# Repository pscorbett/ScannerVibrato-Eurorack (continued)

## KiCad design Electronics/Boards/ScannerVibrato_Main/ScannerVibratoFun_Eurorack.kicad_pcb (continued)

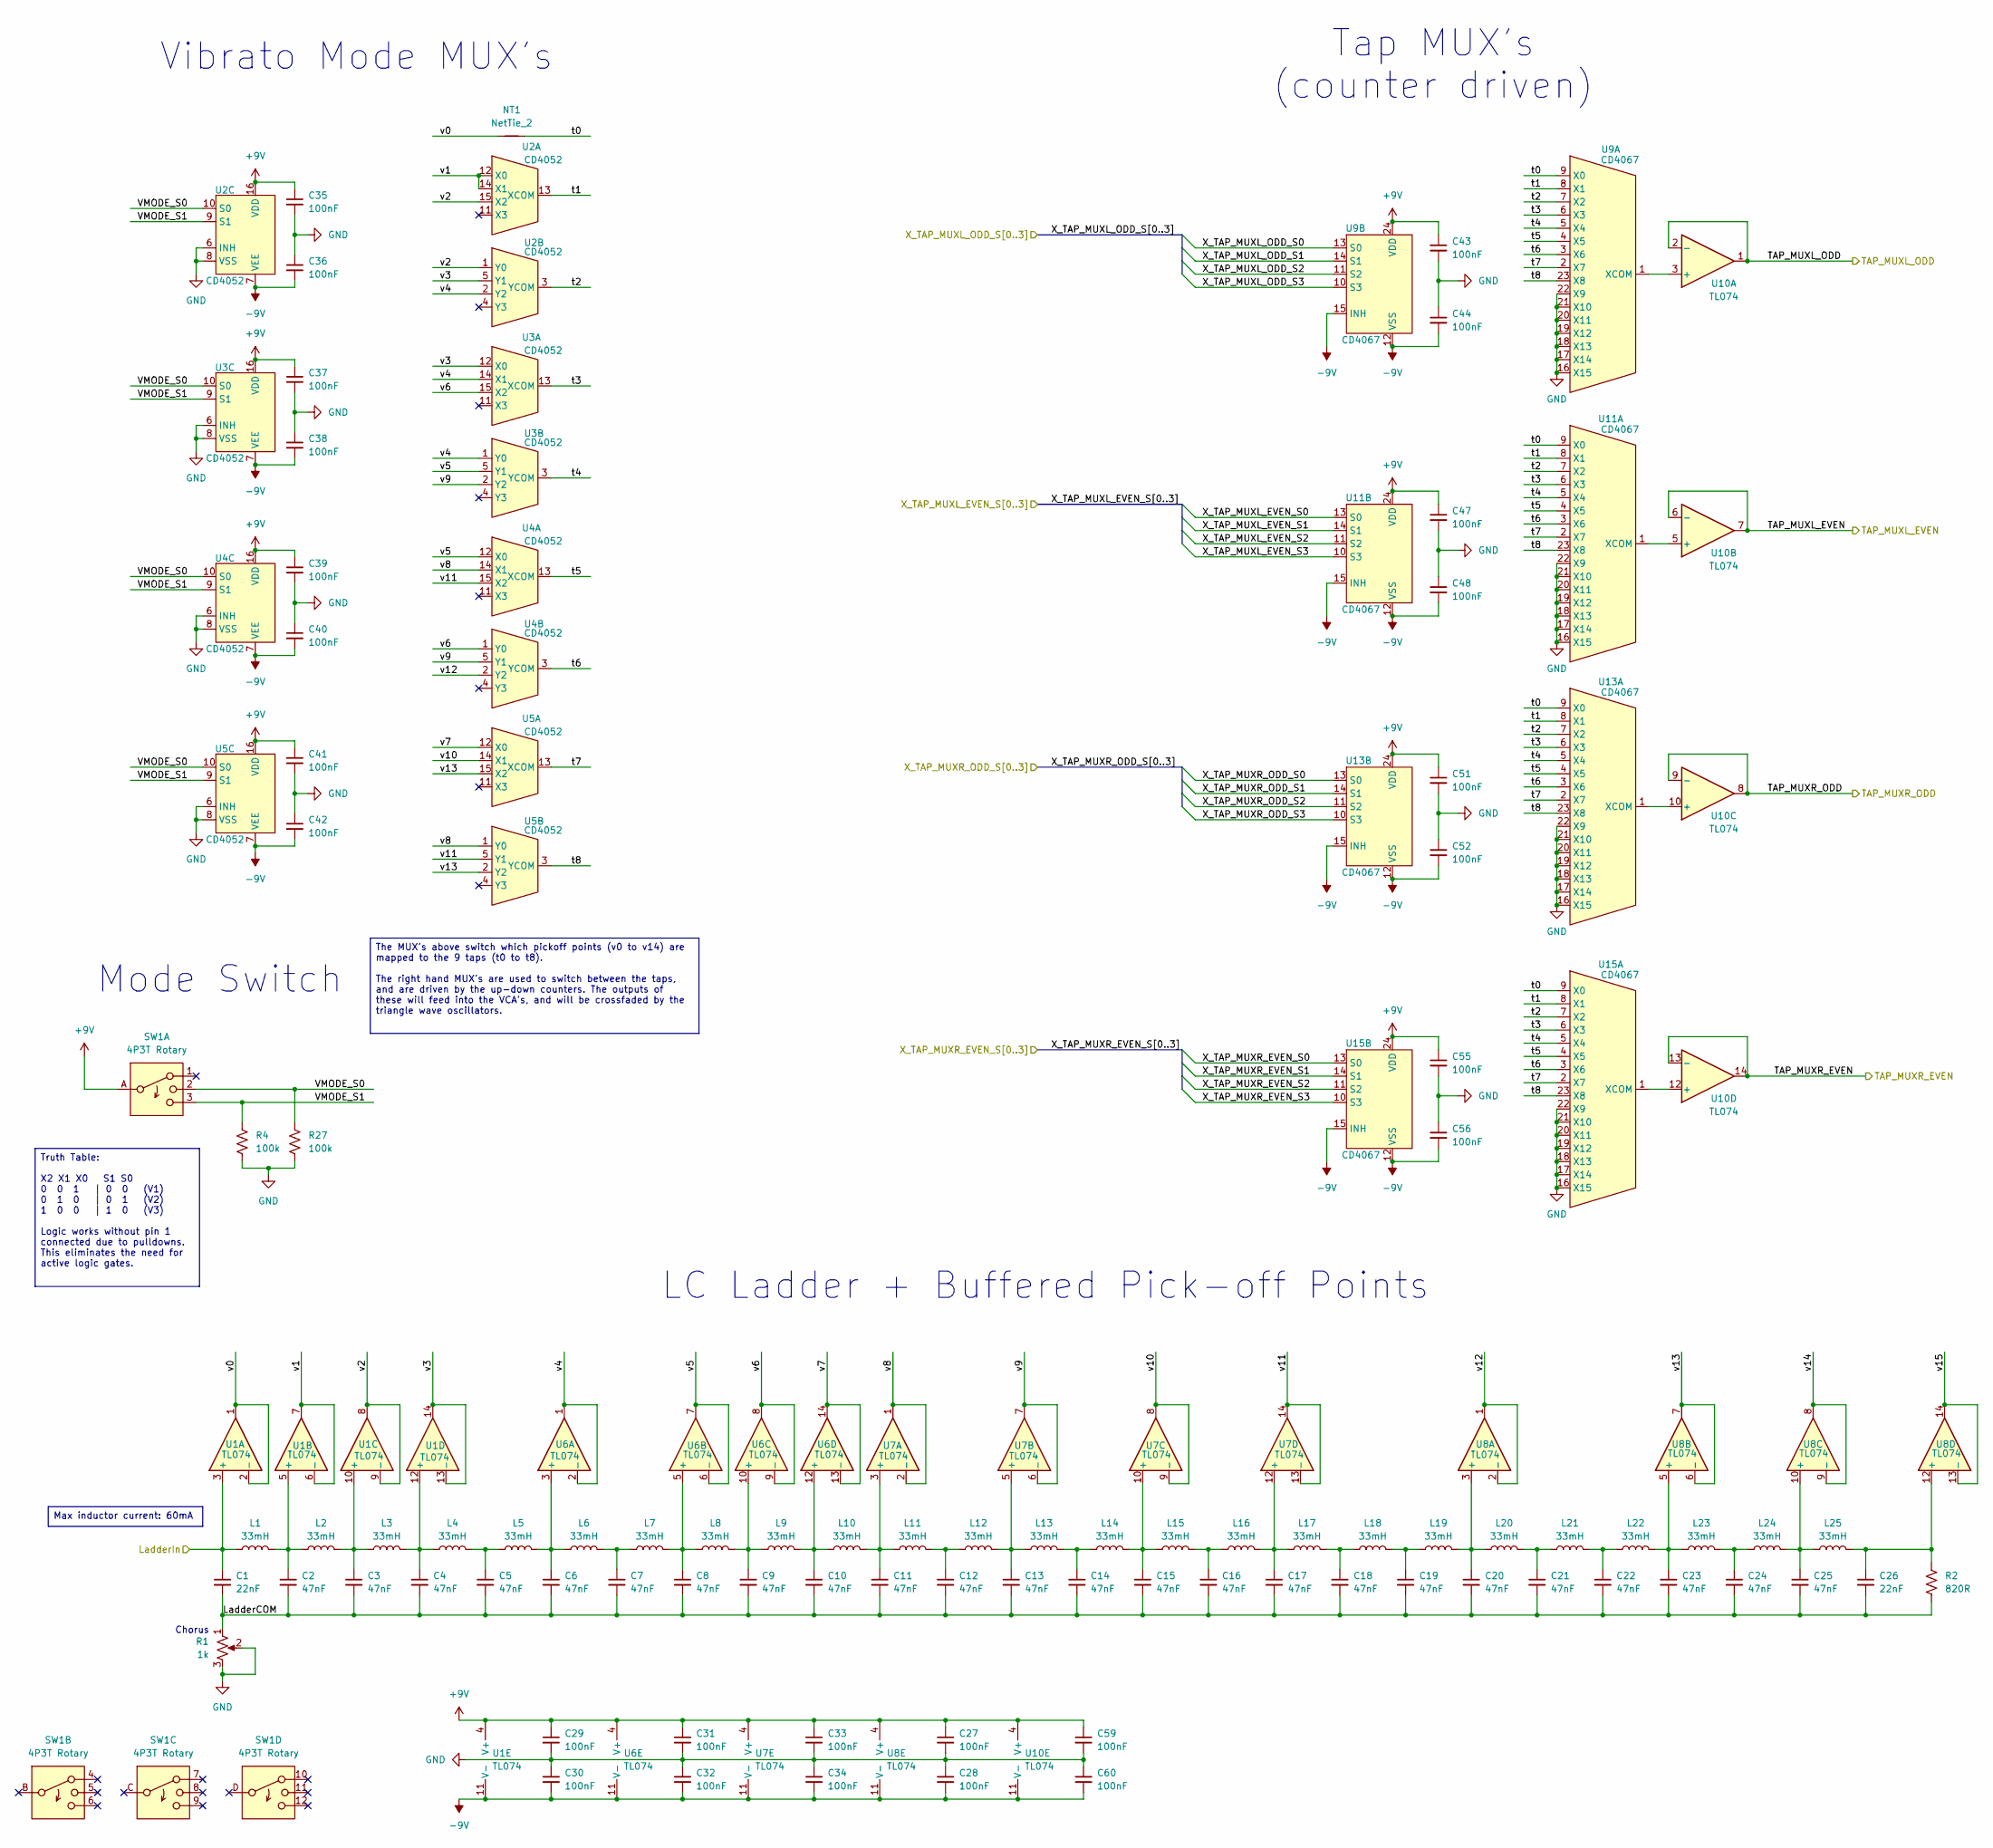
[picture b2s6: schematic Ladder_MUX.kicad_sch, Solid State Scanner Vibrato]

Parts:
C1, C26: 22nF; C_0603_1608Metric
C2, C3, C4, C5, C6, C7, C8, C9, C10, C11, C12, C13, C14, C15, C16, C17, C18, C19, C20, C21, C22, C23, C24, C25: 47nF; C_0603_1608Metric
C27, C28, C29, C30, C31, C32, C33, C34, C35, C36, C37, C38, C39, C40, C41, C42, C43, C44, C47, C48, C51, C52, C55, C56, C59, C60: 100nF; C_0603_1608Metric
L1, L2, L3, L4, L5, L6, L7, L8, L9, L10, L11, L12, L13, L14, L15, L16, L17, L18, L19, L20, L21, L22, L23, L24, L25: 33mH; 1300R_MUR; Part Number 13R336C
NT1: NetTie_2; NetTie-2_SMD_Pad0.5mm
R1: 1k; 16mm-POT-Right-Angle_LL; Part Number RV16AF-4M-15R1-B1K-EV
R2: 820R; R_0603_1608Metric
R4, R27: 100k; R_0603_1608Metric
SW1: 4P3T Rotary; SR2511 1P Hijack; Part Number SR2612F-0403-18R0B-D8-N
U1, U6, U7, U8, U10: TL074; TSSOP-14_4.4x5mm_P0.65mm; Part Number TL074HIPWR
U2, U3, U4, U5: CD4052; TSSOP-16_4.4x5mm_P0.65mm; Part Number CD4052BPWR
U9, U11, U13, U15: CD4067; TSSOP-24_4.4x7.8mm_P0.65mm; Part Number CD4067BPWR

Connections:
+9V: C27.1, C29.1, C31.1, C33.1, C35.1, C37.1, C39.1, C41.1, C43.1, C47.1, C51.1, C55.1, C59.1, SW1.A, U1.4 (V+), U2.16 (VDD), U3.16 (VDD), U4.16 (VDD), U5.16 (VDD), U6.4 (V+), U7.4 (V+), U8.4 (V+), U9.24 (VDD), U10.4 (V+), U11.24 (VDD), U13.24 (VDD), U15.24 (VDD); also elsewhere on the board
-9V: C28.2, C30.2, C32.2, C34.2, C36.2, C38.2, C40.2, C42.2, C44.2, C48.2, C52.2, C56.2, C60.2, U1.11 (V-), U2.7 (VEE), U3.7 (VEE), U4.7 (VEE), U5.7 (VEE), U6.11 (V-), U7.11 (V-), U8.11 (V-), U9.12 (VSS), U9.15 (INH), U10.11 (V-), U11.12 (VSS), U11.15 (INH), U13.12 (VSS), U13.15 (INH), U15.12 (VSS), U15.15 (INH); also elsewhere on the board
/Counters/X_TAP_MUXL_EVEN_S0: U11.13 (S0); also elsewhere on the board
/Counters/X_TAP_MUXL_EVEN_S1: U11.14 (S1); also elsewhere on the board
/Counters/X_TAP_MUXL_EVEN_S2: U11.11 (S2); also elsewhere on the board
/Counters/X_TAP_MUXL_EVEN_S3: U11.10 (S3); also elsewhere on the board
/Counters/X_TAP_MUXL_ODD_S0: U9.13 (S0); also elsewhere on the board
/Counters/X_TAP_MUXL_ODD_S1: U9.14 (S1); also elsewhere on the board
/Counters/X_TAP_MUXL_ODD_S2: U9.11 (S2); also elsewhere on the board
/Counters/X_TAP_MUXL_ODD_S3: U9.10 (S3); also elsewhere on the board
/Counters/X_TAP_MUXR_EVEN_S0: U15.13 (S0); also elsewhere on the board
/Counters/X_TAP_MUXR_EVEN_S1: U15.14 (S1); also elsewhere on the board
/Counters/X_TAP_MUXR_EVEN_S2: U15.11 (S2); also elsewhere on the board
/Counters/X_TAP_MUXR_EVEN_S3: U15.10 (S3); also elsewhere on the board
/Counters/X_TAP_MUXR_ODD_S0: U13.13 (S0); also elsewhere on the board
/Counters/X_TAP_MUXR_ODD_S1: U13.14 (S1); also elsewhere on the board
/Counters/X_TAP_MUXR_ODD_S2: U13.11 (S2); also elsewhere on the board
/Counters/X_TAP_MUXR_ODD_S3: U13.10 (S3); also elsewhere on the board
/Ladder + Mux/LadderCOM: C1.2, C2.2, C3.2, C4.2, C5.2, C6.2, C7.2, C8.2, C9.2, C10.2, C11.2, C12.2, C13.2, C14.2, C15.2, C16.2, C17.2, C18.2, C19.2, C20.2, C21.2, C22.2, C23.2, C24.2, C25.2, C26.2, R1.1, R2.2
/Ladder + Mux/LadderIn: C1.1, L1.1, U1.3 (+); also elsewhere on the board
/Ladder + Mux/TAP_MUXL_EVEN: U10.6 (-), U10.7; also elsewhere on the board
/Ladder + Mux/TAP_MUXL_ODD: U10.1, U10.2 (-); also elsewhere on the board
/Ladder + Mux/TAP_MUXR_EVEN: U10.13 (-), U10.14; also elsewhere on the board
/Ladder + Mux/TAP_MUXR_ODD: U10.8, U10.9 (-); also elsewhere on the board
/Ladder + Mux/VMODE_S0: R27.1, SW1.2, U2.10 (S0), U3.10 (S0), U4.10 (S0), U5.10 (S0)
/Ladder + Mux/VMODE_S1: R4.1, SW1.3, U2.9 (S1), U3.9 (S1), U4.9 (S1), U5.9 (S1)
/Ladder + Mux/t0: NT1.2, U9.9 (X0), U11.9 (X0), U13.9 (X0), U15.9 (X0)
/Ladder + Mux/t1: U2.13 (XCOM), U9.8 (X1), U11.8 (X1), U13.8 (X1), U15.8 (X1)
/Ladder + Mux/t2: U2.3 (YCOM), U9.7 (X2), U11.7 (X2), U13.7 (X2), U15.7 (X2)
/Ladder + Mux/t3: U3.13 (XCOM), U9.6 (X3), U11.6 (X3), U13.6 (X3), U15.6 (X3)
/Ladder + Mux/t4: U3.3 (YCOM), U9.5 (X4), U11.5 (X4), U13.5 (X4), U15.5 (X4)
/Ladder + Mux/t5: U4.13 (XCOM), U9.4 (X5), U11.4 (X5), U13.4 (X5), U15.4 (X5)
/Ladder + Mux/t6: U4.3 (YCOM), U9.3 (X6), U11.3 (X6), U13.3 (X6), U15.3 (X6)
/Ladder + Mux/t7: U5.13 (XCOM), U9.2 (X7), U11.2 (X7), U13.2 (X7), U15.2 (X7)
/Ladder + Mux/t8: U5.3 (YCOM), U9.23 (X8), U11.23 (X8), U13.23 (X8), U15.23 (X8)
/Ladder + Mux/v0: NT1.1, U1.1, U1.2 (-)
/Ladder + Mux/v1: U1.6 (-), U1.7, U2.12 (X0), U2.14 (X1)
/Ladder + Mux/v2: U1.8, U1.9 (-), U2.1 (Y0), U2.15 (X2)
/Ladder + Mux/v3: U1.13 (-), U1.14, U2.5 (Y1), U3.12 (X0)
/Ladder + Mux/v4: U2.2 (Y2), U3.1 (Y0), U3.14 (X1), U6.1, U6.2 (-)
/Ladder + Mux/v5: U3.5 (Y1), U4.12 (X0), U6.6 (-), U6.7
/Ladder + Mux/v6: U3.15 (X2), U4.1 (Y0), U6.8, U6.9 (-)
/Ladder + Mux/v7: U5.12 (X0), U6.13 (-), U6.14
/Ladder + Mux/v8: U4.14 (X1), U5.1 (Y0), U7.1, U7.2 (-)
/Ladder + Mux/v9: U3.2 (Y2), U4.5 (Y1), U7.6 (-), U7.7
/Ladder + Mux/v10: U5.14 (X1), U7.8, U7.9 (-)
/Ladder + Mux/v11: U4.15 (X2), U5.5 (Y1), U7.13 (-), U7.14
/Ladder + Mux/v12: U4.2 (Y2), U8.1, U8.2 (-)
/Ladder + Mux/v13: U5.2 (Y2), U5.15 (X2), U8.6 (-), U8.7
/Ladder + Mux/v14: U8.8, U8.9 (-)
/Ladder + Mux/v15: U8.13 (-), U8.14
GND: C27.2, C28.1, C29.2, C30.1, C31.2, C32.1, C33.2, C34.1, C35.2, C36.1, C37.2, C38.1, C39.2, C40.1, C41.2, C42.1, C43.2, C44.1, C47.2, C48.1, C51.2, C52.1, C55.2, C56.1, C59.2, C60.1, R1.2, R1.3, R4.2, R27.2, U2.6 (INH), U2.8 (VSS), U3.6 (INH), U3.8 (VSS), U4.6 (INH), U4.8 (VSS), U5.6 (INH), U5.8 (VSS), U9.16 (X15), U9.17 (X14), U9.18 (X13), U9.19 (X12), U9.20 (X11), U9.21 (X10), U9.22 (X9), U11.16 (X15), U11.17 (X14), U11.18 (X13), U11.19 (X12), U11.20 (X11), U11.21 (X10), U11.22 (X9), U13.16 (X15), U13.17 (X14), U13.18 (X13), U13.19 (X12), U13.20 (X11), U13.21 (X10), U13.22 (X9), U15.16 (X15), U15.17 (X14), U15.18 (X13), U15.19 (X12), U15.20 (X11), U15.21 (X10), U15.22 (X9); also elsewhere on the board
unnamed: C5.1, L4.2, L5.1
unnamed: C7.1, L6.2, L7.1
unnamed: C12.1, L11.2, L12.1
unnamed: C14.1, L13.2, L14.1
unnamed: C16.1, L15.2, L16.1
unnamed: C18.1, L17.2, L18.1
unnamed: C19.1, L18.2, L19.1
unnamed: C21.1, L20.2, L21.1
unnamed: C22.1, L21.2, L22.1
unnamed: C24.1, L23.2, L24.1
unnamed: C2.1, L1.2, L2.1, U1.5 (+)
unnamed: C3.1, L2.2, L3.1, U1.10 (+)
unnamed: C4.1, L3.2, L4.1, U1.12 (+)
unnamed: C6.1, L5.2, L6.1, U6.3 (+)
unnamed: C8.1, L7.2, L8.1, U6.5 (+)
unnamed: C9.1, L8.2, L9.1, U6.10 (+)
unnamed: C10.1, L9.2, L10.1, U6.12 (+)
unnamed: C11.1, L10.2, L11.1, U7.3 (+)
unnamed: C13.1, L12.2, L13.1, U7.5 (+)
unnamed: C15.1, L14.2, L15.1, U7.10 (+)
unnamed: C17.1, L16.2, L17.1, U7.12 (+)
unnamed: C20.1, L19.2, L20.1, U8.3 (+)
unnamed: C23.1, L22.2, L23.1, U8.5 (+)
unnamed: C25.1, L24.2, L25.1, U8.10 (+)
unnamed: C26.1, L25.2, R2.1, U8.12 (+)
unnamed: U9.1 (XCOM), U10.3 (+)
unnamed: U10.5 (+), U11.1 (XCOM)
unnamed: U10.10 (+), U13.1 (XCOM)
unnamed: U10.12 (+), U15.1 (XCOM)

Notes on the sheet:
Tap MUX's (counter driven)
Mode Switch
Vibrato Mode MUX's
Chorus
LC Ladder + Buffered Pick-off Points
Truth Table: X2 X1 X0 S1 S0 0 0 1 | 0 0 (V1) 0 1 0 | 0 1 (V2) 1 0 0 | 1 0 (V3) Logic works without pin 1 connected due to pulldowns. This eliminates the need for active logic gates.
The MUX's above switch which pickoff points (v0 to v14) are mapped to the 9 taps (t0 to t8). The right hand MUX's are used to switch between the taps, and are driven by the up-down counters. The outputs of these will feed into the VCA's, and will be crossfaded by the triangle wave oscillators.
Max inductor current: 60mA

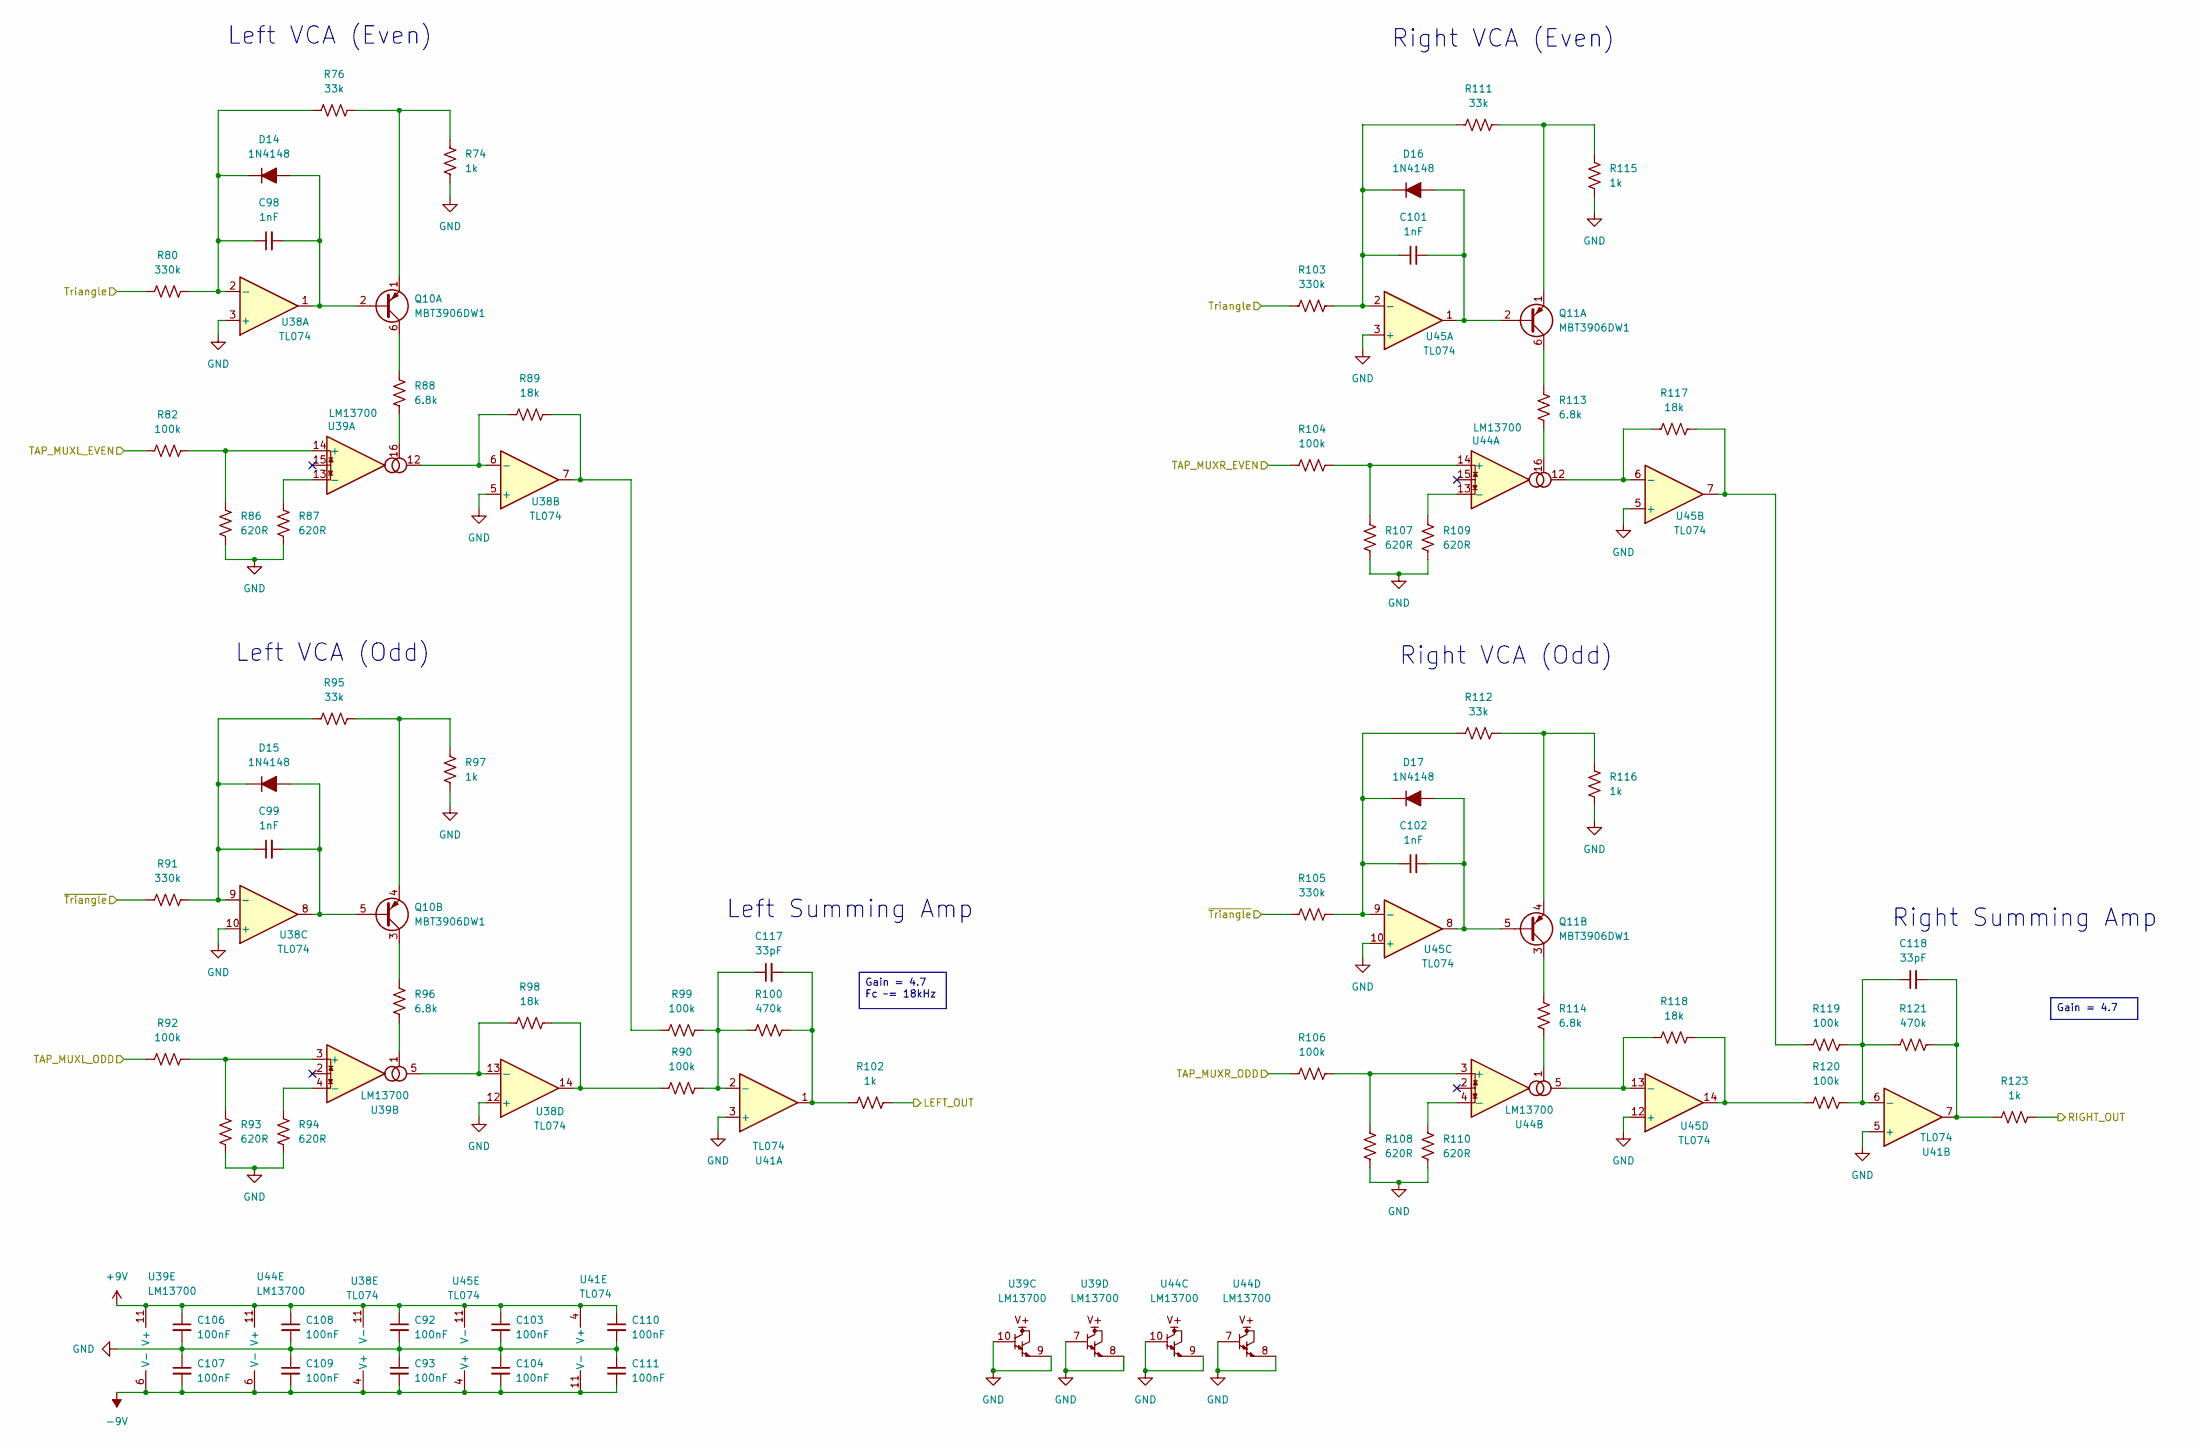
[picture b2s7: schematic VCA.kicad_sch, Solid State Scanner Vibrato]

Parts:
C92, C93, C103, C104, C106, C107, C108, C109, C110, C111: 100nF; C_0603_1608Metric
C98, C99, C101, C102: 1nF; C_0603_1608Metric
C117, C118: 33pF; C_0603_1608Metric
D14, D15, D16, D17: 1N4148; D_SOD-523; Part Number 1N4148WT
Q10, Q11: MBT3906DW1; SOT-363_SC-70-6; Part Number MBT3906DW1T1G
R74, R97, R102, R115, R116, R123: 1k; R_0603_1608Metric
R76, R95, R111, R112: 33k; R_0603_1608Metric
R80, R91, R103, R105: 330k; R_0603_1608Metric
R82, R90, R92, R99, R104, R106, R119, R120: 100k; R_0603_1608Metric
R86, R87, R93, R94, R107, R108, R109, R110: 620R; R_0603_1608Metric
R88, R96, R113, R114: 6.8k; R_0603_1608Metric
R89, R98, R117, R118: 18k; R_0603_1608Metric
R100, R121: 470k; R_0603_1608Metric
U38, U41, U45: TL074; TSSOP-14_4.4x5mm_P0.65mm; Part Number TL074HIPWR
U39, U44: LM13700; SOIC-16_3.9x9.9mm_P1.27mm; Part Number LM13700MX/NOPB

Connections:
+9V: C92.1, C103.1, C106.1, C108.1, C110.1, U38.11 (V-), U39.11 (V+), U41.4 (V+), U44.11 (V+), U45.11 (V-); also elsewhere on the board
-9V: C93.2, C104.2, C107.2, C109.2, C111.2, U38.4 (V+), U39.6 (V-), U41.11 (V-), U44.6 (V-), U45.4 (V+); also elsewhere on the board
/LED Array/Triangle: R80.2, R103.2; also elsewhere on the board
/LED Array/~Triangle: R91.2, R105.2; also elsewhere on the board
/Ladder + Mux/TAP_MUXL_EVEN: R82.2; also elsewhere on the board
/Ladder + Mux/TAP_MUXL_ODD: R92.2; also elsewhere on the board
/Ladder + Mux/TAP_MUXR_EVEN: R104.2; also elsewhere on the board
/Ladder + Mux/TAP_MUXR_ODD: R106.2; also elsewhere on the board
/VCAs/LEFT_OUT: R102.1; also elsewhere on the board
/VCAs/RIGHT_OUT: R123.1; also elsewhere on the board
GND: C92.2, C93.1, C103.2, C104.1, C106.2, C107.1, C108.2, C109.1, C110.2, C111.1, R74.1, R86.1, R87.1, R93.1, R94.1, R97.1, R107.1, R108.1, R109.1, R110.1, R115.1, R116.1, U38.3 (+), U38.5 (+), U38.10 (+), U38.12 (+), U39.7, U39.8, U39.9, U39.10, U41.3 (+), U41.5 (+), U44.7, U44.8, U44.9, U44.10, U45.3 (+), U45.5 (+), U45.10 (+), U45.12 (+); also elsewhere on the board
unnamed: C117.2, R100.1, R102.2, U41.1
unnamed: C118.2, R121.1, R123.2, U41.7
unnamed: C98.2, D14.2 (A), Q10.2 (B1), U38.1
unnamed: C98.1, D14.1 (K), R76.2, R80.1, U38.2 (-)
unnamed: C99.2, D15.2 (A), Q10.5 (B2), U38.8
unnamed: C99.1, D15.1 (K), R91.1, R95.2, U38.9 (-)
unnamed: C101.2, D16.2 (A), Q11.2 (B1), U45.1
unnamed: C101.1, D16.1 (K), R103.1, R111.2, U45.2 (-)
unnamed: C102.2, D17.2 (A), Q11.5 (B2), U45.8
unnamed: C102.1, D17.1 (K), R105.1, R112.2, U45.9 (-)
unnamed: Q10.6 (C1), R88.2
unnamed: Q10.1 (E1), R74.2, R76.1
unnamed: Q10.3 (C2), R96.2
unnamed: Q10.4 (E2), R95.1, R97.2
unnamed: Q11.6 (C1), R113.2
unnamed: Q11.1 (E1), R111.1, R115.2
unnamed: Q11.3 (C2), R114.2
unnamed: Q11.4 (E2), R112.1, R116.2
unnamed: R88.1, U39.16
unnamed: R89.1, R99.2, U38.7
unnamed: R90.2, R98.1, U38.14
unnamed: R96.1, U39.1
unnamed: R113.1, U44.16
unnamed: R114.1, U44.1
unnamed: R117.1, R119.2, U45.7
unnamed: R118.1, R120.2, U45.14
unnamed: R89.2, U38.6 (-), U39.12
unnamed: R98.2, U38.13 (-), U39.5
unnamed: R82.1, R86.2, U39.14 (+)
unnamed: R87.2, U39.13 (-)
unnamed: R92.1, R93.2, U39.3 (+)
unnamed: R94.2, U39.4 (-)
unnamed: C117.1, R90.1, R99.1, R100.2, U41.2 (-)
unnamed: C118.1, R119.1, R120.1, R121.2, U41.6 (-)
unnamed: R104.1, R107.2, U44.14 (+)
unnamed: R109.2, U44.13 (-)
unnamed: R106.1, R108.2, U44.3 (+)
unnamed: R110.2, U44.4 (-)
unnamed: R117.2, U44.12, U45.6 (-)
unnamed: R118.2, U44.5, U45.13 (-)

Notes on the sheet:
Right VCA (Even)
Left VCA (Odd)
Right Summing Amp
Right VCA (Odd)
Left Summing Amp
Left VCA (Even)
Gain = 4.7 Fc ~= 18kHz
Gain = 4.7

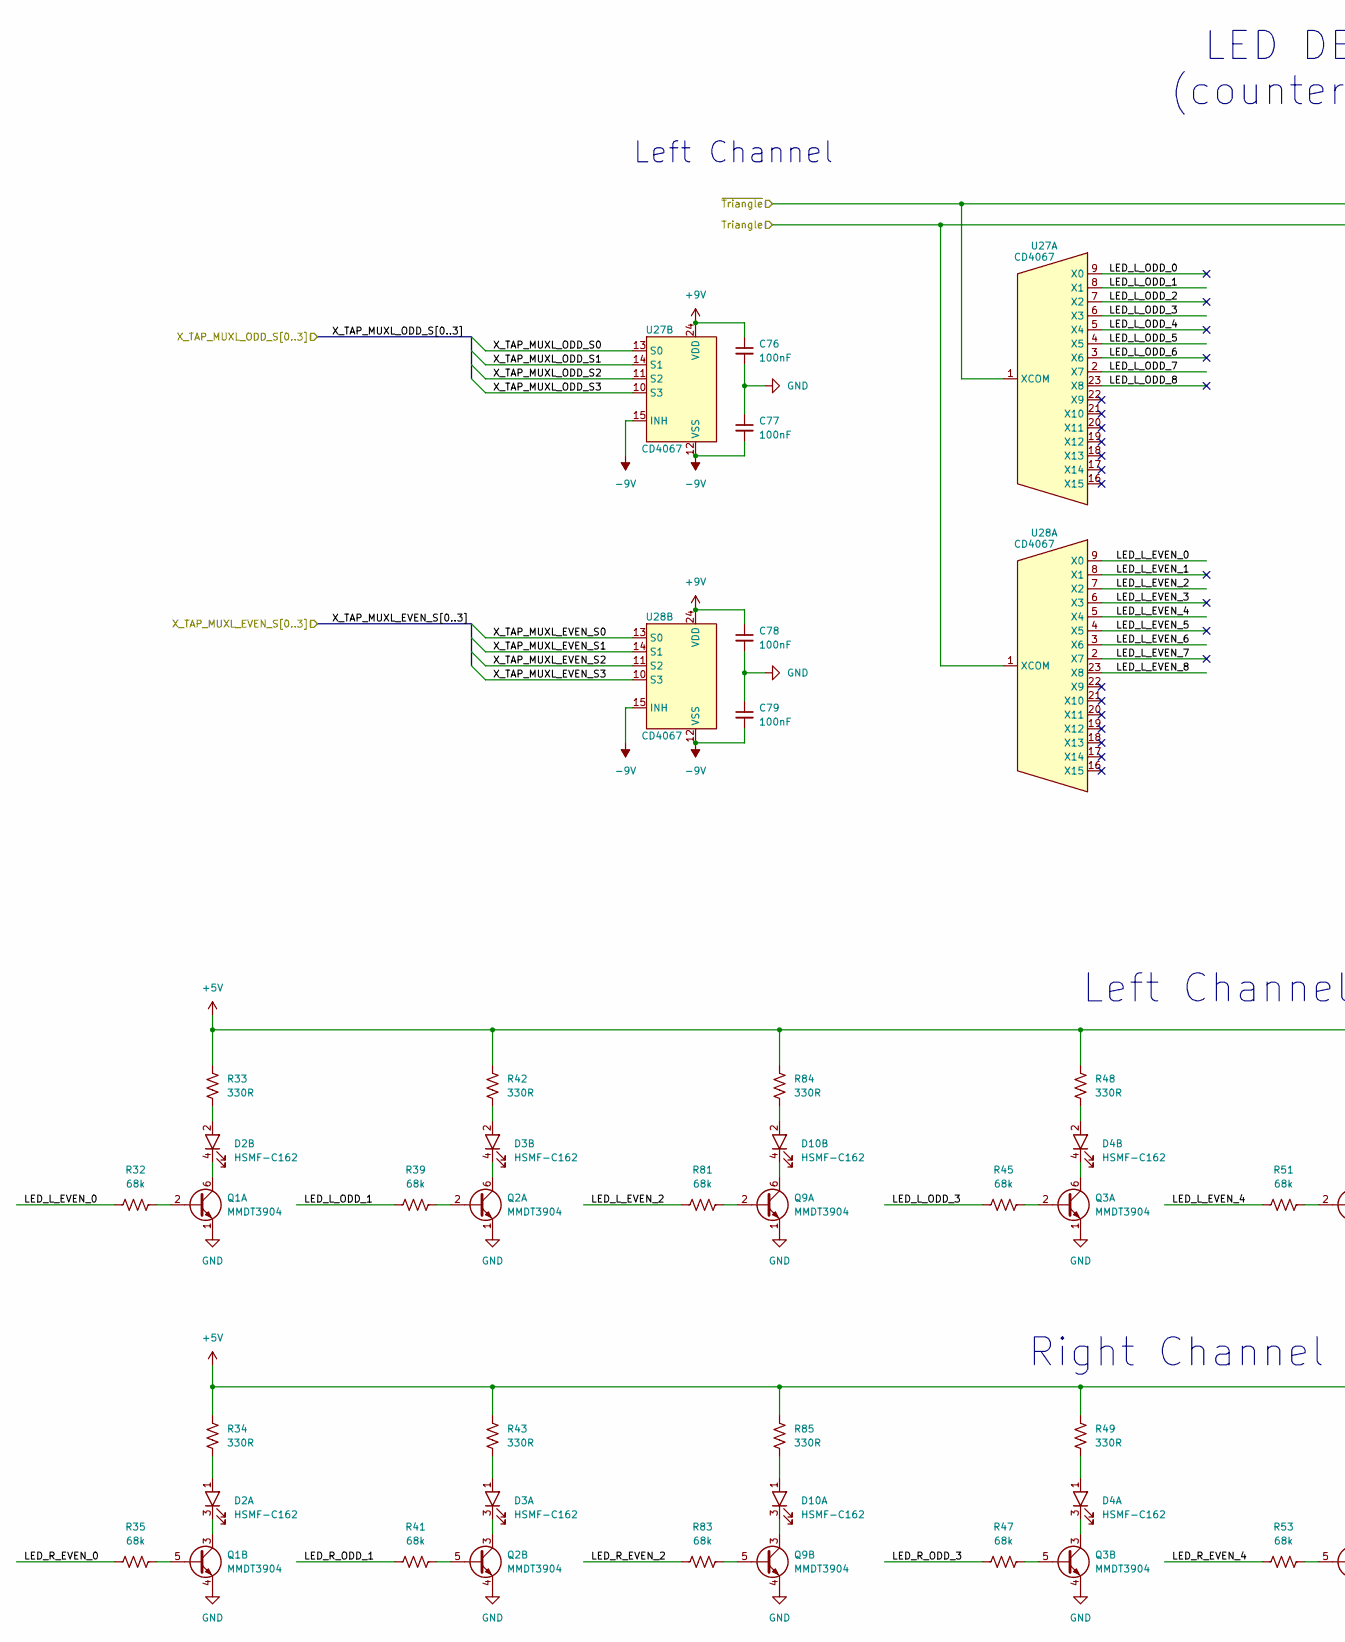
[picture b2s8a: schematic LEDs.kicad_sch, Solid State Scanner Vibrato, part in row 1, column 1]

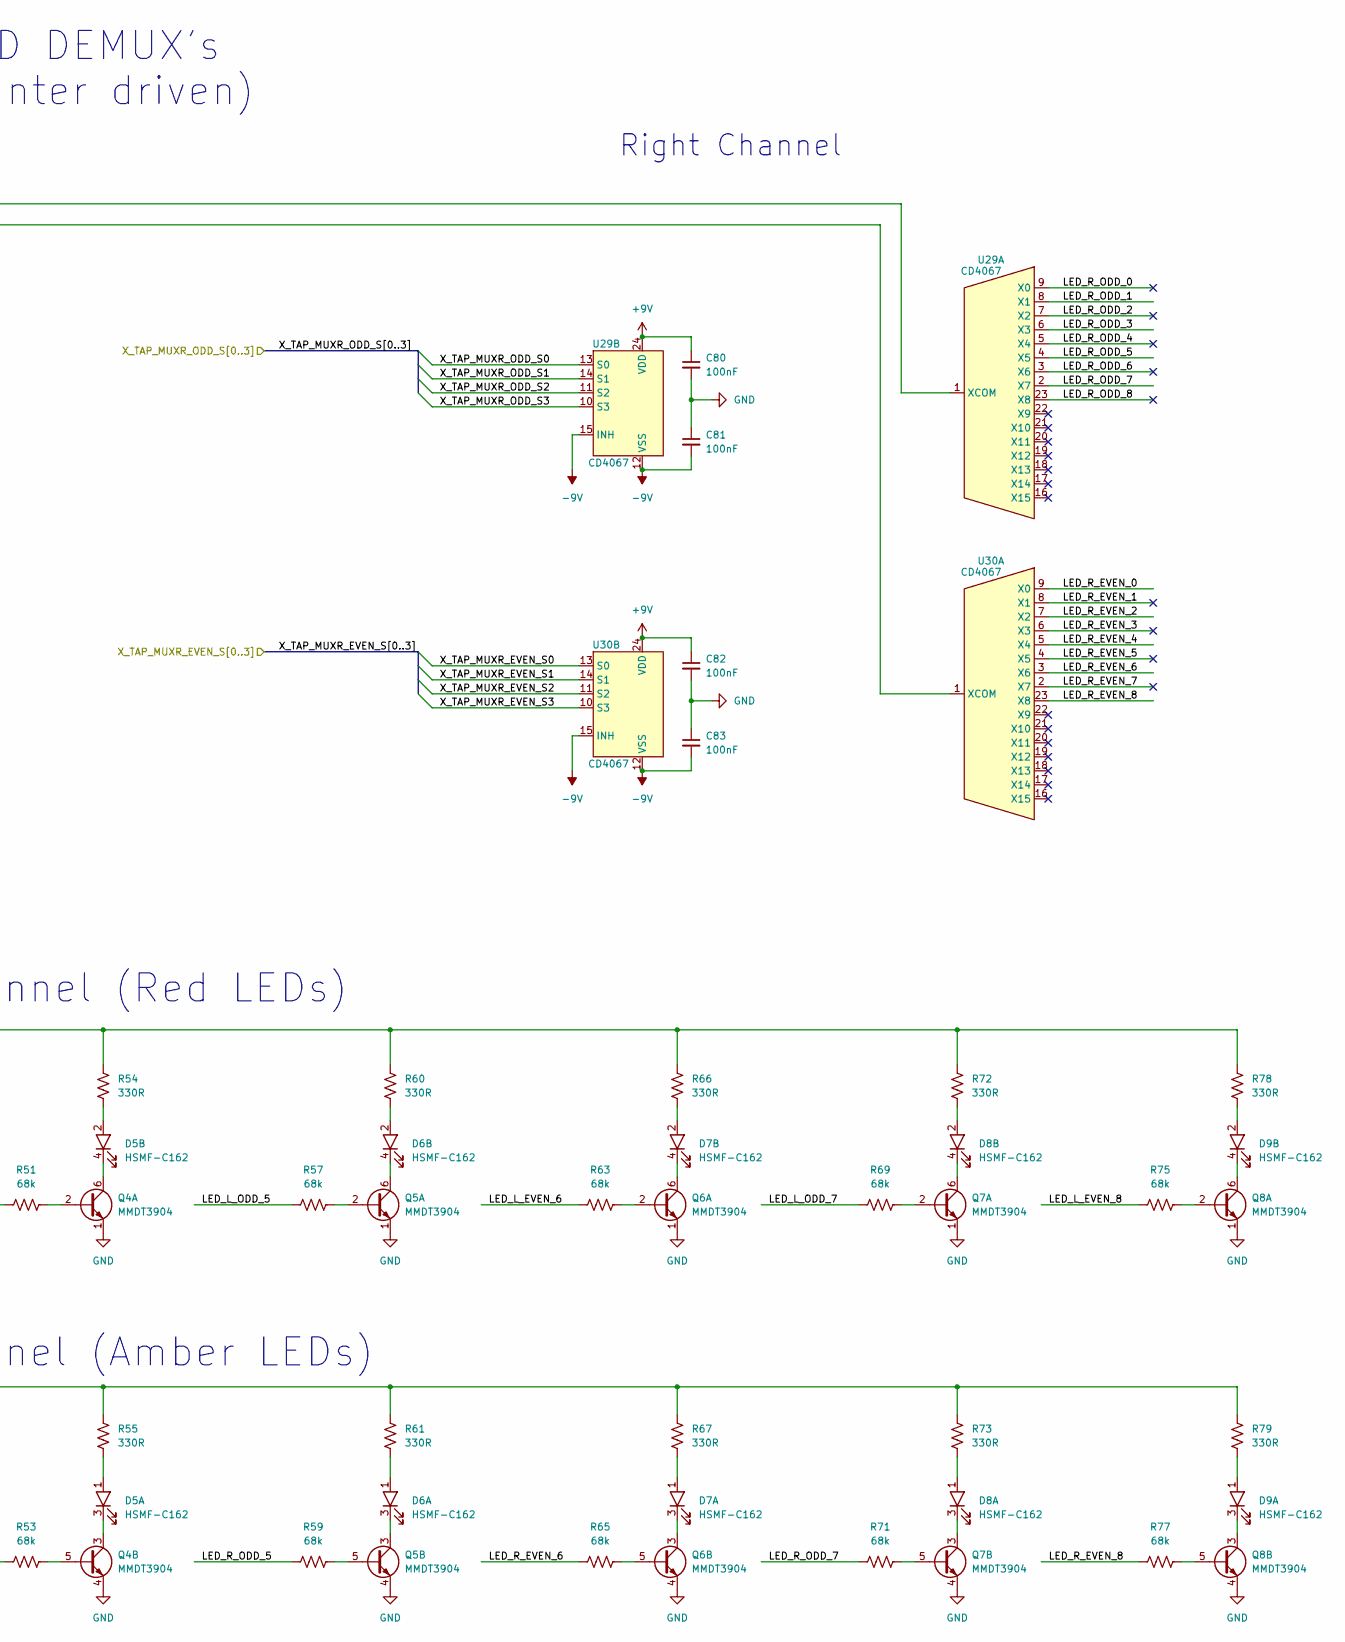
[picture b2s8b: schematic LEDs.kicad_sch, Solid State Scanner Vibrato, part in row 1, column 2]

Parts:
C76, C77, C78, C79, C80, C81, C82, C83: 100nF; C_0603_1608Metric
D2, D3, D4, D5, D6, D7, D8, D9, D10: HSMF-C162; LED_HSMF-C162; Part Number HSMF-C162
Q1, Q2, Q3, Q4, Q5, Q6, Q7, Q8, Q9: MMDT3904; SOT-363_SC-70-6
R32, R35, R39, R41, R45, R47, R51, R53, R57, R59, R63, R65, R69, R71, R75, R77, R81, R83: 68k; R_0603_1608Metric
R33, R34, R42, R43, R48, R49, R54, R55, R60, R61, R66, R67, R72, R73, R78, R79, R84, R85: 330R; R_0603_1608Metric
U27, U28, U29, U30: CD4067; TSSOP-24_4.4x7.8mm_P0.65mm; Part Number CD4067BPWR

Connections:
+5V: R33.1, R34.1, R42.1, R43.1, R48.1, R49.1, R54.1, R55.1, R60.1, R61.1, R66.1, R67.1, R72.1, R73.1, R78.1, R79.1, R84.1, R85.1; also elsewhere on the board
+9V: C76.1, C78.1, C80.1, C82.1, U27.24 (VDD), U28.24 (VDD), U29.24 (VDD), U30.24 (VDD); also elsewhere on the board
-9V: C77.2, C79.2, C81.2, C83.2, U27.12 (VSS), U27.15 (INH), U28.12 (VSS), U28.15 (INH), U29.12 (VSS), U29.15 (INH), U30.12 (VSS), U30.15 (INH); also elsewhere on the board
/Counters/X_TAP_MUXL_EVEN_S0: U28.13 (S0); also elsewhere on the board
/Counters/X_TAP_MUXL_EVEN_S1: U28.14 (S1); also elsewhere on the board
/Counters/X_TAP_MUXL_EVEN_S2: U28.11 (S2); also elsewhere on the board
/Counters/X_TAP_MUXL_EVEN_S3: U28.10 (S3); also elsewhere on the board
/Counters/X_TAP_MUXL_ODD_S0: U27.13 (S0); also elsewhere on the board
/Counters/X_TAP_MUXL_ODD_S1: U27.14 (S1); also elsewhere on the board
/Counters/X_TAP_MUXL_ODD_S2: U27.11 (S2); also elsewhere on the board
/Counters/X_TAP_MUXL_ODD_S3: U27.10 (S3); also elsewhere on the board
/Counters/X_TAP_MUXR_EVEN_S0: U30.13 (S0); also elsewhere on the board
/Counters/X_TAP_MUXR_EVEN_S1: U30.14 (S1); also elsewhere on the board
/Counters/X_TAP_MUXR_EVEN_S2: U30.11 (S2); also elsewhere on the board
/Counters/X_TAP_MUXR_EVEN_S3: U30.10 (S3); also elsewhere on the board
/Counters/X_TAP_MUXR_ODD_S0: U29.13 (S0); also elsewhere on the board
/Counters/X_TAP_MUXR_ODD_S1: U29.14 (S1); also elsewhere on the board
/Counters/X_TAP_MUXR_ODD_S2: U29.11 (S2); also elsewhere on the board
/Counters/X_TAP_MUXR_ODD_S3: U29.10 (S3); also elsewhere on the board
/LED Array/LED_L_EVEN_0: R32.1, U28.9 (X0)
/LED Array/LED_L_EVEN_1: U28.8 (X1)
/LED Array/LED_L_EVEN_2: R81.1, U28.7 (X2)
/LED Array/LED_L_EVEN_3: U28.6 (X3)
/LED Array/LED_L_EVEN_4: R51.1, U28.5 (X4)
/LED Array/LED_L_EVEN_5: U28.4 (X5)
/LED Array/LED_L_EVEN_6: R63.1, U28.3 (X6)
/LED Array/LED_L_EVEN_7: U28.2 (X7)
/LED Array/LED_L_EVEN_8: R75.1, U28.23 (X8)
/LED Array/LED_L_ODD_0: U27.9 (X0)
/LED Array/LED_L_ODD_1: R39.1, U27.8 (X1)
/LED Array/LED_L_ODD_2: U27.7 (X2)
/LED Array/LED_L_ODD_3: R45.1, U27.6 (X3)
/LED Array/LED_L_ODD_4: U27.5 (X4)
/LED Array/LED_L_ODD_5: R57.1, U27.4 (X5)
/LED Array/LED_L_ODD_6: U27.3 (X6)
/LED Array/LED_L_ODD_7: R69.1, U27.2 (X7)
/LED Array/LED_L_ODD_8: U27.23 (X8)
/LED Array/LED_R_EVEN_0: R35.1, U30.9 (X0)
/LED Array/LED_R_EVEN_1: U30.8 (X1)
/LED Array/LED_R_EVEN_2: R83.1, U30.7 (X2)
/LED Array/LED_R_EVEN_3: U30.6 (X3)
/LED Array/LED_R_EVEN_4: R53.1, U30.5 (X4)
/LED Array/LED_R_EVEN_5: U30.4 (X5)
/LED Array/LED_R_EVEN_6: R65.1, U30.3 (X6)
/LED Array/LED_R_EVEN_7: U30.2 (X7)
/LED Array/LED_R_EVEN_8: R77.1, U30.23 (X8)
/LED Array/LED_R_ODD_0: U29.9 (X0)
/LED Array/LED_R_ODD_1: R41.1, U29.8 (X1)
/LED Array/LED_R_ODD_2: U29.7 (X2)
/LED Array/LED_R_ODD_3: R47.1, U29.6 (X3)
/LED Array/LED_R_ODD_4: U29.5 (X4)
/LED Array/LED_R_ODD_5: R59.1, U29.4 (X5)
/LED Array/LED_R_ODD_6: U29.3 (X6)
/LED Array/LED_R_ODD_7: R71.1, U29.2 (X7)
/LED Array/LED_R_ODD_8: U29.23 (X8)
/LED Array/Triangle: U28.1 (XCOM), U30.1 (XCOM); also elsewhere on the board
/LED Array/~Triangle: U27.1 (XCOM), U29.1 (XCOM); also elsewhere on the board
GND: C76.2, C77.1, C78.2, C79.1, C80.2, C81.1, C82.2, C83.1, Q1.1 (E1), Q1.4 (E2), Q2.1 (E1), Q2.4 (E2), Q3.1 (E1), Q3.4 (E2), Q4.1 (E1), Q4.4 (E2), Q5.1 (E1), Q5.4 (E2), Q6.1 (E1), Q6.4 (E2), Q7.1 (E1), Q7.4 (E2), Q8.1 (E1), Q8.4 (E2), Q9.1 (E1), Q9.4 (E2); also elsewhere on the board
unnamed: D2.1 (A_A), R34.2
unnamed: D2.3 (A_K), Q1.3 (C2)
unnamed: D2.2 (R_A), R33.2
unnamed: D2.4 (R_K), Q1.6 (C1)
unnamed: D3.1 (A_A), R43.2
unnamed: D3.3 (A_K), Q2.3 (C2)
unnamed: D3.2 (R_A), R42.2
unnamed: D3.4 (R_K), Q2.6 (C1)
unnamed: D4.1 (A_A), R49.2
unnamed: D4.3 (A_K), Q3.3 (C2)
unnamed: D4.2 (R_A), R48.2
unnamed: D4.4 (R_K), Q3.6 (C1)
unnamed: D5.1 (A_A), R55.2
unnamed: D5.3 (A_K), Q4.3 (C2)
unnamed: D5.2 (R_A), R54.2
unnamed: D5.4 (R_K), Q4.6 (C1)
unnamed: D6.1 (A_A), R61.2
unnamed: D6.3 (A_K), Q5.3 (C2)
unnamed: D6.2 (R_A), R60.2
unnamed: D6.4 (R_K), Q5.6 (C1)
unnamed: D7.1 (A_A), R67.2
unnamed: D7.3 (A_K), Q6.3 (C2)
unnamed: D7.2 (R_A), R66.2
unnamed: D7.4 (R_K), Q6.6 (C1)
unnamed: D8.1 (A_A), R73.2
unnamed: D8.3 (A_K), Q7.3 (C2)
unnamed: D8.2 (R_A), R72.2
unnamed: D8.4 (R_K), Q7.6 (C1)
unnamed: D9.1 (A_A), R79.2
unnamed: D9.3 (A_K), Q8.3 (C2)
unnamed: D9.2 (R_A), R78.2
unnamed: D9.4 (R_K), Q8.6 (C1)
unnamed: D10.1 (A_A), R85.2
unnamed: D10.3 (A_K), Q9.3 (C2)
unnamed: D10.2 (R_A), R84.2
unnamed: D10.4 (R_K), Q9.6 (C1)
unnamed: Q1.2 (B1), R32.2
unnamed: Q1.5 (B2), R35.2
unnamed: Q2.2 (B1), R39.2
unnamed: Q2.5 (B2), R41.2
unnamed: Q3.2 (B1), R45.2
unnamed: Q3.5 (B2), R47.2
unnamed: Q4.2 (B1), R51.2
unnamed: Q4.5 (B2), R53.2
unnamed: Q5.2 (B1), R57.2
unnamed: Q5.5 (B2), R59.2
unnamed: Q6.2 (B1), R63.2
unnamed: Q6.5 (B2), R65.2
unnamed: Q7.2 (B1), R69.2
unnamed: Q7.5 (B2), R71.2
unnamed: Q8.2 (B1), R75.2
unnamed: Q8.5 (B2), R77.2
unnamed: Q9.2 (B1), R81.2
unnamed: Q9.5 (B2), R83.2

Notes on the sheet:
Right Channel
Left Channel (Red LEDs)
LED DEMUX's (counter driven)
Right Channel (Amber LEDs)
Left Channel
